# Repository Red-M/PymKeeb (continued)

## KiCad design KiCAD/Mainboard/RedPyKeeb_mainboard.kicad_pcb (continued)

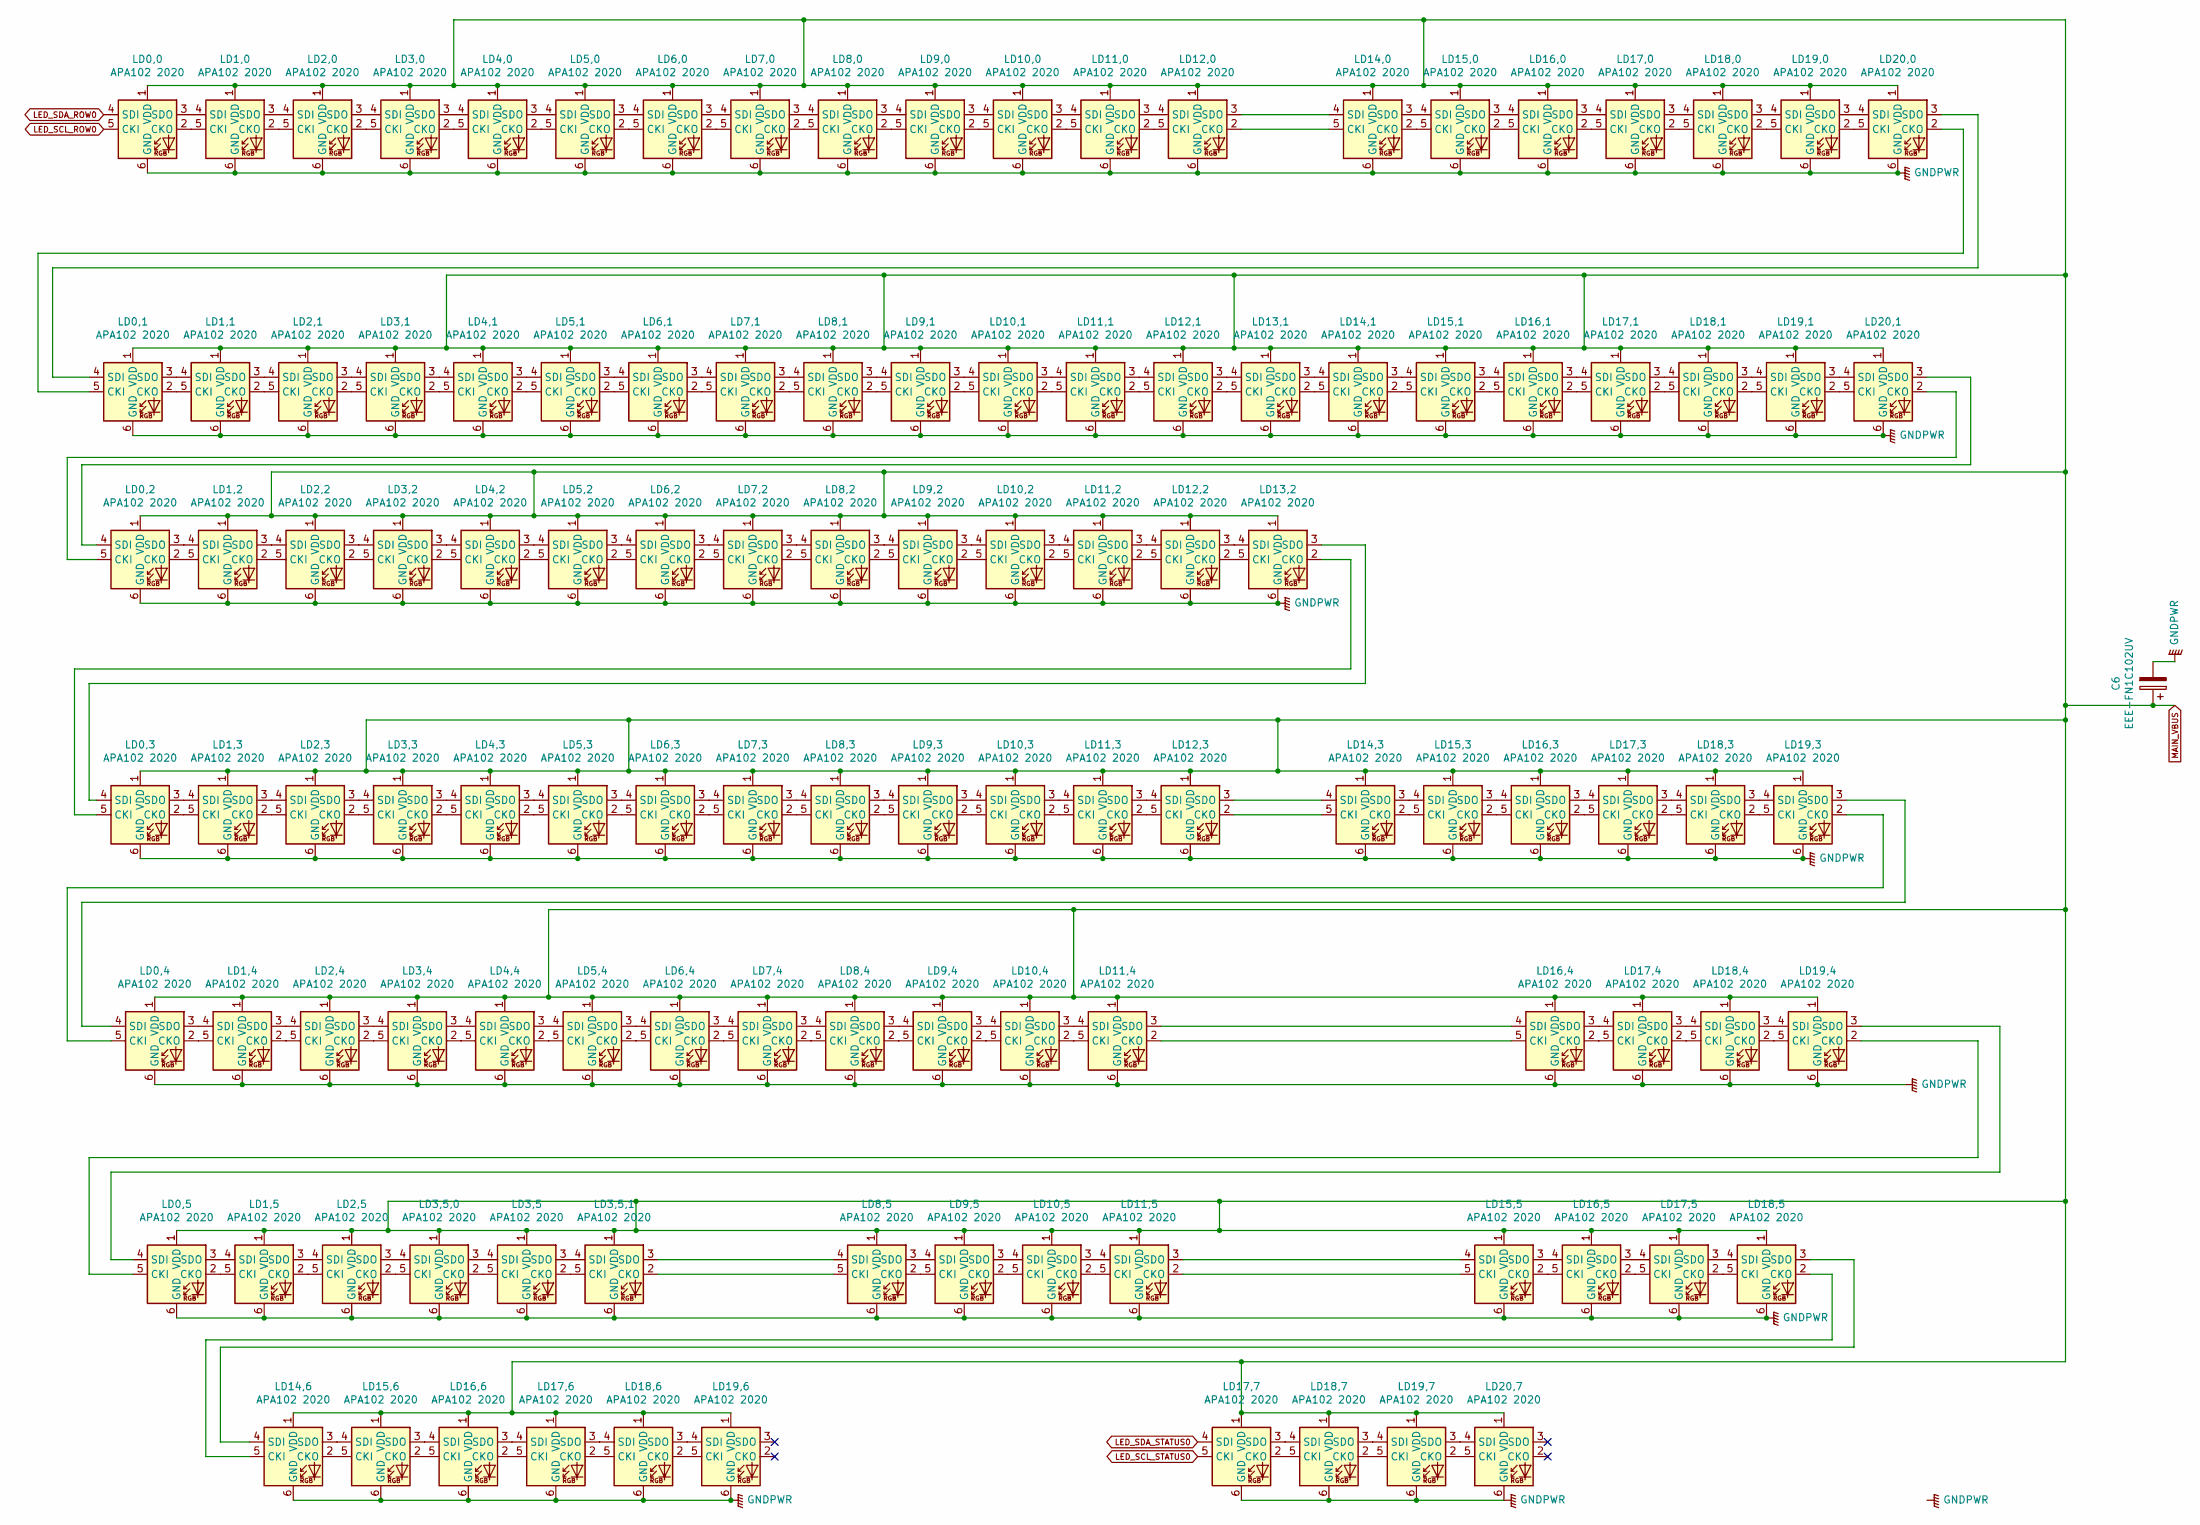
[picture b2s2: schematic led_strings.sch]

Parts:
C6: EEE-FN1C102UV; CP_Elec_10x10; Mouser No 667-EEE-FN1C102UV
LD0,0, LD0,1, LD0,2, LD0,3, LD0,4, LD0,5, LD1,0, LD1,1, LD1,2, LD1,3, LD1,4, LD1,5, LD2,0, LD2,1, LD2,2, LD2,3, LD2,4, LD2,5, LD3,0, LD3,1, LD3,2, LD3,3, LD3,4, LD3,5, LD3,5,0, LD3,5,1, LD4,0, LD4,1, LD4,2, LD4,3, LD4,4, LD5,0, LD5,1, LD5,2, LD5,3, LD5,4, LD6,0, LD6,1, LD6,2, LD6,3, LD6,4, LD7,0, LD7,1, LD7,2, LD7,3, LD7,4, LD8,0, LD8,1, LD8,2, LD8,3, LD8,4, LD8,5, LD9,0, LD9,1, LD9,2, LD9,3, LD9,4, LD9,5, LD10,0, LD10,1, LD10,2, LD10,3, LD10,4, LD10,5, LD11,0, LD11,1, LD11,2, LD11,3, LD11,4, LD11,5, LD12,0, LD12,1, LD12,2, LD12,3, LD13,1, LD13,2, LD14,0, LD14,1, LD14,3, LD14,6, LD15,0, LD15,1, LD15,3, LD15,5, LD15,6, LD16,0, LD16,1, LD16,3, LD16,4, LD16,5, LD16,6, LD17,0, LD17,1, LD17,3, LD17,4, LD17,5, LD17,6, LD17,7, LD18,0, LD18,1, LD18,3, LD18,4, LD18,5, LD18,6, LD18,7, LD19,0, LD19,1, LD19,3, LD19,4, LD19,6, LD19,7, LD20,0, LD20,1, LD20,7: APA102 2020; LED-APA102-2020; Mouser No 485-3587

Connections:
GNDPWR: C6.2, LD0,0.6 (GND), LD0,1.6 (GND), LD0,2.6 (GND), LD0,3.6 (GND), LD0,4.6 (GND), LD0,5.6 (GND), LD1,0.6 (GND), LD1,1.6 (GND), LD1,2.6 (GND), LD1,3.6 (GND), LD1,4.6 (GND), LD1,5.6 (GND), LD2,0.6 (GND), LD2,1.6 (GND), LD2,2.6 (GND), LD2,3.6 (GND), LD2,4.6 (GND), LD2,5.6 (GND), LD3,0.6 (GND), LD3,1.6 (GND), LD3,2.6 (GND), LD3,3.6 (GND), LD3,4.6 (GND), LD3,5.6 (GND), LD3,5,0.6 (GND), LD3,5,1.6 (GND), LD4,0.6 (GND), LD4,1.6 (GND), LD4,2.6 (GND), LD4,3.6 (GND), LD4,4.6 (GND), LD5,0.6 (GND), LD5,1.6 (GND), LD5,2.6 (GND), LD5,3.6 (GND), LD5,4.6 (GND), LD6,0.6 (GND), LD6,1.6 (GND), LD6,2.6 (GND), LD6,3.6 (GND), LD6,4.6 (GND), LD7,0.6 (GND), LD7,1.6 (GND), LD7,2.6 (GND), LD7,3.6 (GND), LD7,4.6 (GND), LD8,0.6 (GND), LD8,1.6 (GND), LD8,2.6 (GND), LD8,3.6 (GND), LD8,4.6 (GND), LD8,5.6 (GND), LD9,0.6 (GND), LD9,1.6 (GND), LD9,2.6 (GND), LD9,3.6 (GND), LD9,4.6 (GND), LD9,5.6 (GND), LD10,0.6 (GND), LD10,1.6 (GND), LD10,2.6 (GND), LD10,3.6 (GND), LD10,4.6 (GND), LD10,5.6 (GND), LD11,0.6 (GND), LD11,1.6 (GND), LD11,2.6 (GND), LD11,3.6 (GND), LD11,4.6 (GND), LD11,5.6 (GND), LD12,0.6 (GND), LD12,1.6 (GND), LD12,2.6 (GND), LD12,3.6 (GND), LD13,1.6 (GND), LD13,2.6 (GND), LD14,0.6 (GND), LD14,1.6 (GND), LD14,3.6 (GND), LD14,6.6 (GND), LD15,0.6 (GND), LD15,1.6 (GND), LD15,3.6 (GND), LD15,5.6 (GND), LD15,6.6 (GND), LD16,0.6 (GND), LD16,1.6 (GND), LD16,3.6 (GND), LD16,4.6 (GND), LD16,5.6 (GND), LD16,6.6 (GND), LD17,0.6 (GND), LD17,1.6 (GND), LD17,3.6 (GND), LD17,4.6 (GND), LD17,5.6 (GND), LD17,6.6 (GND), LD17,7.6 (GND), LD18,0.6 (GND), LD18,1.6 (GND), LD18,3.6 (GND), LD18,4.6 (GND), LD18,5.6 (GND), LD18,6.6 (GND), LD18,7.6 (GND), LD19,0.6 (GND), LD19,1.6 (GND), LD19,3.6 (GND), LD19,4.6 (GND), LD19,6.6 (GND), LD19,7.6 (GND), LD20,0.6 (GND), LD20,1.6 (GND), LD20,7.6 (GND); also elsewhere on the board
LED_SCL_ROW0: LD0,0.5 (CKI); also elsewhere on the board
LED_SCL_STATUS0: LD17,7.5 (CKI); also elsewhere on the board
LED_SDA_ROW0: LD0,0.4 (SDI); also elsewhere on the board
LED_SDA_STATUS0: LD17,7.4 (SDI); also elsewhere on the board
MAIN_VBUS: C6.1, LD0,0.1 (VDD), LD0,1.1 (VDD), LD0,2.1 (VDD), LD0,3.1 (VDD), LD0,4.1 (VDD), LD0,5.1 (VDD), LD1,0.1 (VDD), LD1,1.1 (VDD), LD1,2.1 (VDD), LD1,3.1 (VDD), LD1,4.1 (VDD), LD1,5.1 (VDD), LD2,0.1 (VDD), LD2,1.1 (VDD), LD2,2.1 (VDD), LD2,3.1 (VDD), LD2,4.1 (VDD), LD2,5.1 (VDD), LD3,0.1 (VDD), LD3,1.1 (VDD), LD3,2.1 (VDD), LD3,3.1 (VDD), LD3,4.1 (VDD), LD3,5.1 (VDD), LD3,5,0.1 (VDD), LD3,5,1.1 (VDD), LD4,0.1 (VDD), LD4,1.1 (VDD), LD4,2.1 (VDD), LD4,3.1 (VDD), LD4,4.1 (VDD), LD5,0.1 (VDD), LD5,1.1 (VDD), LD5,2.1 (VDD), LD5,3.1 (VDD), LD5,4.1 (VDD), LD6,0.1 (VDD), LD6,1.1 (VDD), LD6,2.1 (VDD), LD6,3.1 (VDD), LD6,4.1 (VDD), LD7,0.1 (VDD), LD7,1.1 (VDD), LD7,2.1 (VDD), LD7,3.1 (VDD), LD7,4.1 (VDD), LD8,0.1 (VDD), LD8,1.1 (VDD), LD8,2.1 (VDD), LD8,3.1 (VDD), LD8,4.1 (VDD), LD8,5.1 (VDD), LD9,0.1 (VDD), LD9,1.1 (VDD), LD9,2.1 (VDD), LD9,3.1 (VDD), LD9,4.1 (VDD), LD9,5.1 (VDD), LD10,0.1 (VDD), LD10,1.1 (VDD), LD10,2.1 (VDD), LD10,3.1 (VDD), LD10,4.1 (VDD), LD10,5.1 (VDD), LD11,0.1 (VDD), LD11,1.1 (VDD), LD11,2.1 (VDD), LD11,3.1 (VDD), LD11,4.1 (VDD), LD11,5.1 (VDD), LD12,0.1 (VDD), LD12,1.1 (VDD), LD12,2.1 (VDD), LD12,3.1 (VDD), LD13,1.1 (VDD), LD13,2.1 (VDD), LD14,0.1 (VDD), LD14,1.1 (VDD), LD14,3.1 (VDD), LD14,6.1 (VDD), LD15,0.1 (VDD), LD15,1.1 (VDD), LD15,3.1 (VDD), LD15,5.1 (VDD), LD15,6.1 (VDD), LD16,0.1 (VDD), LD16,1.1 (VDD), LD16,3.1 (VDD), LD16,4.1 (VDD), LD16,5.1 (VDD), LD16,6.1 (VDD), LD17,0.1 (VDD), LD17,1.1 (VDD), LD17,3.1 (VDD), LD17,4.1 (VDD), LD17,5.1 (VDD), LD17,6.1 (VDD), LD17,7.1 (VDD), LD18,0.1 (VDD), LD18,1.1 (VDD), LD18,3.1 (VDD), LD18,4.1 (VDD), LD18,5.1 (VDD), LD18,6.1 (VDD), LD18,7.1 (VDD), LD19,0.1 (VDD), LD19,1.1 (VDD), LD19,3.1 (VDD), LD19,4.1 (VDD), LD19,6.1 (VDD), LD19,7.1 (VDD), LD20,0.1 (VDD), LD20,1.1 (VDD), LD20,7.1 (VDD); also elsewhere on the board
unnamed: LD0,0.2 (CKO), LD1,0.5 (CKI)
unnamed: LD0,0.3 (SDO), LD1,0.4 (SDI)
unnamed: LD0,1.2 (CKO), LD1,1.5 (CKI)
unnamed: LD0,1.3 (SDO), LD1,1.4 (SDI)
unnamed: LD0,1.4 (SDI), LD20,0.3 (SDO)
unnamed: LD0,1.5 (CKI), LD20,0.2 (CKO)
unnamed: LD0,2.2 (CKO), LD1,2.5 (CKI)
unnamed: LD0,2.3 (SDO), LD1,2.4 (SDI)
unnamed: LD0,2.4 (SDI), LD20,1.3 (SDO)
unnamed: LD0,2.5 (CKI), LD20,1.2 (CKO)
unnamed: LD0,3.2 (CKO), LD1,3.5 (CKI)
unnamed: LD0,3.3 (SDO), LD1,3.4 (SDI)
unnamed: LD0,3.4 (SDI), LD13,2.3 (SDO)
unnamed: LD0,3.5 (CKI), LD13,2.2 (CKO)
unnamed: LD0,4.2 (CKO), LD1,4.5 (CKI)
unnamed: LD0,4.3 (SDO), LD1,4.4 (SDI)
unnamed: LD0,4.4 (SDI), LD19,3.3 (SDO)
unnamed: LD0,4.5 (CKI), LD19,3.2 (CKO)
unnamed: LD0,5.2 (CKO), LD1,5.5 (CKI)
unnamed: LD0,5.3 (SDO), LD1,5.4 (SDI)
unnamed: LD0,5.4 (SDI), LD19,4.3 (SDO)
unnamed: LD0,5.5 (CKI), LD19,4.2 (CKO)
unnamed: LD1,0.2 (CKO), LD2,0.5 (CKI)
unnamed: LD1,0.3 (SDO), LD2,0.4 (SDI)
unnamed: LD1,1.2 (CKO), LD2,1.5 (CKI)
unnamed: LD1,1.3 (SDO), LD2,1.4 (SDI)
unnamed: LD1,2.2 (CKO), LD2,2.5 (CKI)
unnamed: LD1,2.3 (SDO), LD2,2.4 (SDI)
unnamed: LD1,3.2 (CKO), LD2,3.5 (CKI)
unnamed: LD1,3.3 (SDO), LD2,3.4 (SDI)
unnamed: LD1,4.2 (CKO), LD2,4.5 (CKI)
unnamed: LD1,4.3 (SDO), LD2,4.4 (SDI)
unnamed: LD1,5.2 (CKO), LD2,5.5 (CKI)
unnamed: LD1,5.3 (SDO), LD2,5.4 (SDI)
unnamed: LD2,0.2 (CKO), LD3,0.5 (CKI)
unnamed: LD2,0.3 (SDO), LD3,0.4 (SDI)
unnamed: LD2,1.2 (CKO), LD3,1.5 (CKI)
unnamed: LD2,1.3 (SDO), LD3,1.4 (SDI)
unnamed: LD2,2.2 (CKO), LD3,2.5 (CKI)
unnamed: LD2,2.3 (SDO), LD3,2.4 (SDI)
unnamed: LD2,3.2 (CKO), LD3,3.5 (CKI)
unnamed: LD2,3.3 (SDO), LD3,3.4 (SDI)
unnamed: LD2,4.2 (CKO), LD3,4.5 (CKI)
unnamed: LD2,4.3 (SDO), LD3,4.4 (SDI)
unnamed: LD2,5.2 (CKO), LD3,5,0.5 (CKI)
unnamed: LD2,5.3 (SDO), LD3,5,0.4 (SDI)
unnamed: LD3,0.2 (CKO), LD4,0.5 (CKI)
unnamed: LD3,0.3 (SDO), LD4,0.4 (SDI)
unnamed: LD3,1.2 (CKO), LD4,1.5 (CKI)
unnamed: LD3,1.3 (SDO), LD4,1.4 (SDI)
unnamed: LD3,2.2 (CKO), LD4,2.5 (CKI)
unnamed: LD3,2.3 (SDO), LD4,2.4 (SDI)
unnamed: LD3,3.2 (CKO), LD4,3.5 (CKI)
unnamed: LD3,3.3 (SDO), LD4,3.4 (SDI)
unnamed: LD3,4.2 (CKO), LD4,4.5 (CKI)
unnamed: LD3,4.3 (SDO), LD4,4.4 (SDI)
unnamed: LD3,5.5 (CKI), LD3,5,0.2 (CKO)
unnamed: LD3,5.4 (SDI), LD3,5,0.3 (SDO)
unnamed: LD3,5,1.2 (CKO), LD8,5.5 (CKI)
unnamed: LD3,5,1.3 (SDO), LD8,5.4 (SDI)
unnamed: LD3,5.3 (SDO), LD3,5,1.4 (SDI)
unnamed: LD3,5.2 (CKO), LD3,5,1.5 (CKI)
unnamed: LD4,0.2 (CKO), LD5,0.5 (CKI)
unnamed: LD4,0.3 (SDO), LD5,0.4 (SDI)
unnamed: LD4,1.2 (CKO), LD5,1.5 (CKI)
unnamed: LD4,1.3 (SDO), LD5,1.4 (SDI)
unnamed: LD4,2.2 (CKO), LD5,2.5 (CKI)
unnamed: LD4,2.3 (SDO), LD5,2.4 (SDI)
unnamed: LD4,3.2 (CKO), LD5,3.5 (CKI)
unnamed: LD4,3.3 (SDO), LD5,3.4 (SDI)
unnamed: LD4,4.2 (CKO), LD5,4.5 (CKI)
unnamed: LD4,4.3 (SDO), LD5,4.4 (SDI)
unnamed: LD5,0.2 (CKO), LD6,0.5 (CKI)
unnamed: LD5,0.3 (SDO), LD6,0.4 (SDI)
unnamed: LD5,1.2 (CKO), LD6,1.5 (CKI)
unnamed: LD5,1.3 (SDO), LD6,1.4 (SDI)
unnamed: LD5,2.2 (CKO), LD6,2.5 (CKI)
unnamed: LD5,2.3 (SDO), LD6,2.4 (SDI)
unnamed: LD5,3.2 (CKO), LD6,3.5 (CKI)
unnamed: LD5,3.3 (SDO), LD6,3.4 (SDI)
unnamed: LD5,4.2 (CKO), LD6,4.5 (CKI)
unnamed: LD5,4.3 (SDO), LD6,4.4 (SDI)
unnamed: LD6,0.2 (CKO), LD7,0.5 (CKI)
unnamed: LD6,0.3 (SDO), LD7,0.4 (SDI)
unnamed: LD6,1.2 (CKO), LD7,1.5 (CKI)
unnamed: LD6,1.3 (SDO), LD7,1.4 (SDI)
unnamed: LD6,2.2 (CKO), LD7,2.5 (CKI)
unnamed: LD6,2.3 (SDO), LD7,2.4 (SDI)
unnamed: LD6,3.2 (CKO), LD7,3.5 (CKI)
unnamed: LD6,3.3 (SDO), LD7,3.4 (SDI)
unnamed: LD6,4.2 (CKO), LD7,4.5 (CKI)
unnamed: LD6,4.3 (SDO), LD7,4.4 (SDI)
unnamed: LD7,0.2 (CKO), LD8,0.5 (CKI)
unnamed: LD7,0.3 (SDO), LD8,0.4 (SDI)
unnamed: LD7,1.2 (CKO), LD8,1.5 (CKI)
unnamed: LD7,1.3 (SDO), LD8,1.4 (SDI)
unnamed: LD7,2.2 (CKO), LD8,2.5 (CKI)
unnamed: LD7,2.3 (SDO), LD8,2.4 (SDI)
unnamed: LD7,3.2 (CKO), LD8,3.5 (CKI)
unnamed: LD7,3.3 (SDO), LD8,3.4 (SDI)
unnamed: LD7,4.2 (CKO), LD8,4.5 (CKI)
unnamed: LD7,4.3 (SDO), LD8,4.4 (SDI)
unnamed: LD8,0.2 (CKO), LD9,0.5 (CKI)
unnamed: LD8,0.3 (SDO), LD9,0.4 (SDI)
unnamed: LD8,1.2 (CKO), LD9,1.5 (CKI)
unnamed: LD8,1.3 (SDO), LD9,1.4 (SDI)
unnamed: LD8,2.2 (CKO), LD9,2.5 (CKI)
unnamed: LD8,2.3 (SDO), LD9,2.4 (SDI)
unnamed: LD8,3.2 (CKO), LD9,3.5 (CKI)
unnamed: LD8,3.3 (SDO), LD9,3.4 (SDI)
unnamed: LD8,4.2 (CKO), LD9,4.5 (CKI)
unnamed: LD8,4.3 (SDO), LD9,4.4 (SDI)
unnamed: LD8,5.2 (CKO), LD9,5.5 (CKI)
unnamed: LD8,5.3 (SDO), LD9,5.4 (SDI)
unnamed: LD10,0.2 (CKO), LD11,0.5 (CKI)
unnamed: LD10,0.3 (SDO), LD11,0.4 (SDI)
unnamed: LD9,0.3 (SDO), LD10,0.4 (SDI)
unnamed: LD9,0.2 (CKO), LD10,0.5 (CKI)
unnamed: LD10,1.2 (CKO), LD11,1.5 (CKI)
unnamed: LD10,1.3 (SDO), LD11,1.4 (SDI)
unnamed: LD9,1.3 (SDO), LD10,1.4 (SDI)
unnamed: LD9,1.2 (CKO), LD10,1.5 (CKI)
unnamed: LD10,2.2 (CKO), LD11,2.5 (CKI)
unnamed: LD10,2.3 (SDO), LD11,2.4 (SDI)
unnamed: LD9,2.3 (SDO), LD10,2.4 (SDI)
unnamed: LD9,2.2 (CKO), LD10,2.5 (CKI)
unnamed: LD10,3.2 (CKO), LD11,3.5 (CKI)
unnamed: LD10,3.3 (SDO), LD11,3.4 (SDI)
unnamed: LD9,3.3 (SDO), LD10,3.4 (SDI)
unnamed: LD9,3.2 (CKO), LD10,3.5 (CKI)
unnamed: LD10,4.2 (CKO), LD11,4.5 (CKI)
unnamed: LD10,4.3 (SDO), LD11,4.4 (SDI)
unnamed: LD9,4.3 (SDO), LD10,4.4 (SDI)
unnamed: LD9,4.2 (CKO), LD10,4.5 (CKI)
unnamed: LD10,5.2 (CKO), LD11,5.5 (CKI)
unnamed: LD10,5.3 (SDO), LD11,5.4 (SDI)
unnamed: LD9,5.3 (SDO), LD10,5.4 (SDI)
unnamed: LD9,5.2 (CKO), LD10,5.5 (CKI)
unnamed: LD11,0.2 (CKO), LD12,0.5 (CKI)
unnamed: LD11,0.3 (SDO), LD12,0.4 (SDI)
unnamed: LD11,1.2 (CKO), LD12,1.5 (CKI)
unnamed: LD11,1.3 (SDO), LD12,1.4 (SDI)
unnamed: LD11,2.2 (CKO), LD12,2.5 (CKI)
unnamed: LD11,2.3 (SDO), LD12,2.4 (SDI)
unnamed: LD11,3.2 (CKO), LD12,3.5 (CKI)
unnamed: LD11,3.3 (SDO), LD12,3.4 (SDI)
unnamed: LD11,4.2 (CKO), LD16,4.5 (CKI)
unnamed: LD11,4.3 (SDO), LD16,4.4 (SDI)
unnamed: LD11,5.2 (CKO), LD15,5.5 (CKI)
unnamed: LD11,5.3 (SDO), LD15,5.4 (SDI)
unnamed: LD12,0.2 (CKO), LD14,0.5 (CKI)
unnamed: LD12,0.3 (SDO), LD14,0.4 (SDI)
unnamed: LD12,1.2 (CKO), LD13,1.5 (CKI)
unnamed: LD12,1.3 (SDO), LD13,1.4 (SDI)
unnamed: LD12,2.2 (CKO), LD13,2.5 (CKI)
unnamed: LD12,2.3 (SDO), LD13,2.4 (SDI)
unnamed: LD12,3.2 (CKO), LD14,3.5 (CKI)
unnamed: LD12,3.3 (SDO), LD14,3.4 (SDI)
unnamed: LD13,1.2 (CKO), LD14,1.5 (CKI)
unnamed: LD13,1.3 (SDO), LD14,1.4 (SDI)
unnamed: LD14,0.2 (CKO), LD15,0.5 (CKI)
unnamed: LD14,0.3 (SDO), LD15,0.4 (SDI)
unnamed: LD14,1.2 (CKO), LD15,1.5 (CKI)
unnamed: LD14,1.3 (SDO), LD15,1.4 (SDI)
unnamed: LD14,3.2 (CKO), LD15,3.5 (CKI)
unnamed: LD14,3.3 (SDO), LD15,3.4 (SDI)
unnamed: LD14,6.2 (CKO), LD15,6.5 (CKI)
unnamed: LD14,6.3 (SDO), LD15,6.4 (SDI)
unnamed: LD14,6.4 (SDI), LD18,5.3 (SDO)
unnamed: LD14,6.5 (CKI), LD18,5.2 (CKO)
unnamed: LD15,0.2 (CKO), LD16,0.5 (CKI)
unnamed: LD15,0.3 (SDO), LD16,0.4 (SDI)
unnamed: LD15,1.2 (CKO), LD16,1.5 (CKI)
unnamed: LD15,1.3 (SDO), LD16,1.4 (SDI)
unnamed: LD15,3.2 (CKO), LD16,3.5 (CKI)
unnamed: LD15,3.3 (SDO), LD16,3.4 (SDI)
unnamed: LD15,5.2 (CKO), LD16,5.5 (CKI)
unnamed: LD15,5.3 (SDO), LD16,5.4 (SDI)
unnamed: LD15,6.2 (CKO), LD16,6.5 (CKI)
unnamed: LD15,6.3 (SDO), LD16,6.4 (SDI)
unnamed: LD16,0.2 (CKO), LD17,0.5 (CKI)
unnamed: LD16,0.3 (SDO), LD17,0.4 (SDI)
unnamed: LD16,1.2 (CKO), LD17,1.5 (CKI)
unnamed: LD16,1.3 (SDO), LD17,1.4 (SDI)
unnamed: LD16,3.2 (CKO), LD17,3.5 (CKI)
unnamed: LD16,3.3 (SDO), LD17,3.4 (SDI)
unnamed: LD16,4.2 (CKO), LD17,4.5 (CKI)
unnamed: LD16,4.3 (SDO), LD17,4.4 (SDI)
unnamed: LD16,5.2 (CKO), LD17,5.5 (CKI)
unnamed: LD16,5.3 (SDO), LD17,5.4 (SDI)
unnamed: LD16,6.2 (CKO), LD17,6.5 (CKI)
unnamed: LD16,6.3 (SDO), LD17,6.4 (SDI)
unnamed: LD17,0.2 (CKO), LD18,0.5 (CKI)
unnamed: LD17,0.3 (SDO), LD18,0.4 (SDI)
unnamed: LD17,1.2 (CKO), LD18,1.5 (CKI)
unnamed: LD17,1.3 (SDO), LD18,1.4 (SDI)
unnamed: LD17,3.2 (CKO), LD18,3.5 (CKI)
unnamed: LD17,3.3 (SDO), LD18,3.4 (SDI)
unnamed: LD17,4.2 (CKO), LD18,4.5 (CKI)
unnamed: LD17,4.3 (SDO), LD18,4.4 (SDI)
unnamed: LD17,5.2 (CKO), LD18,5.5 (CKI)
unnamed: LD17,5.3 (SDO), LD18,5.4 (SDI)
unnamed: LD17,6.2 (CKO), LD18,6.5 (CKI)
unnamed: LD17,6.3 (SDO), LD18,6.4 (SDI)
unnamed: LD17,7.2 (CKO), LD18,7.5 (CKI)
unnamed: LD17,7.3 (SDO), LD18,7.4 (SDI)
unnamed: LD18,0.2 (CKO), LD19,0.5 (CKI)
unnamed: LD18,0.3 (SDO), LD19,0.4 (SDI)
unnamed: LD18,1.2 (CKO), LD19,1.5 (CKI)
unnamed: LD18,1.3 (SDO), LD19,1.4 (SDI)
unnamed: LD18,3.2 (CKO), LD19,3.5 (CKI)
unnamed: LD18,3.3 (SDO), LD19,3.4 (SDI)
unnamed: LD18,4.2 (CKO), LD19,4.5 (CKI)
unnamed: LD18,4.3 (SDO), LD19,4.4 (SDI)
unnamed: LD18,6.2 (CKO), LD19,6.5 (CKI)
unnamed: LD18,6.3 (SDO), LD19,6.4 (SDI)
unnamed: LD18,7.2 (CKO), LD19,7.5 (CKI)
unnamed: LD18,7.3 (SDO), LD19,7.4 (SDI)
unnamed: LD19,0.2 (CKO), LD20,0.5 (CKI)
unnamed: LD19,0.3 (SDO), LD20,0.4 (SDI)
unnamed: LD19,1.2 (CKO), LD20,1.5 (CKI)
unnamed: LD19,1.3 (SDO), LD20,1.4 (SDI)
unnamed: LD19,7.2 (CKO), LD20,7.5 (CKI)
unnamed: LD19,7.3 (SDO), LD20,7.4 (SDI)

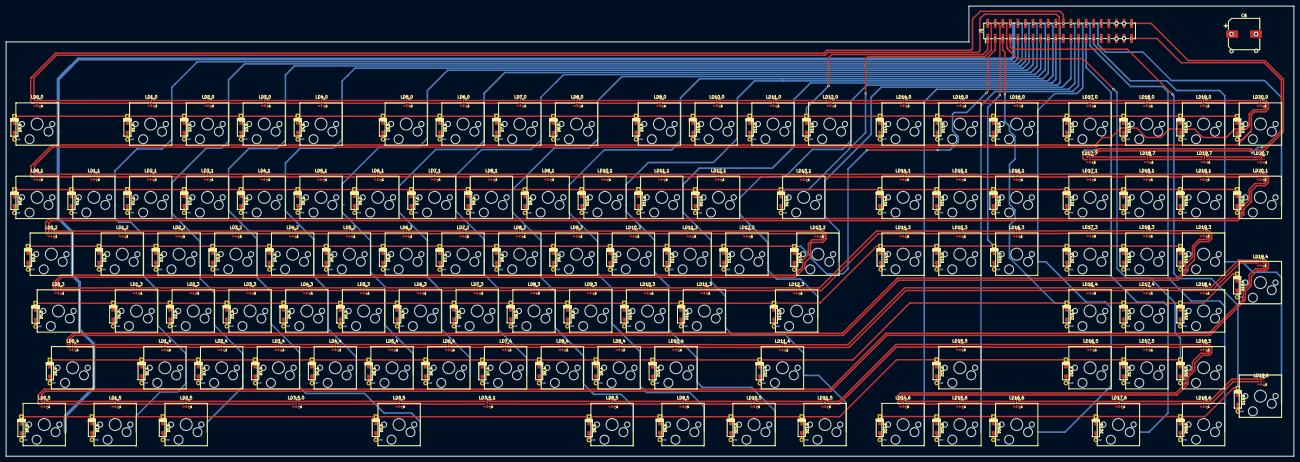
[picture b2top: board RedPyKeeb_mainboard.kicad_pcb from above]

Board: 4 copper layers, 432.0 x 151.0 mm, 333 parts (1 on the bottom side), 366 nets.

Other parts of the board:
C6#2: EEE-FN1C102UV; CP_Elec_10x10

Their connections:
GNDPWR: C6#2.2; also elsewhere on the board
MAIN_VBUS: C6#2.1; also elsewhere on the board

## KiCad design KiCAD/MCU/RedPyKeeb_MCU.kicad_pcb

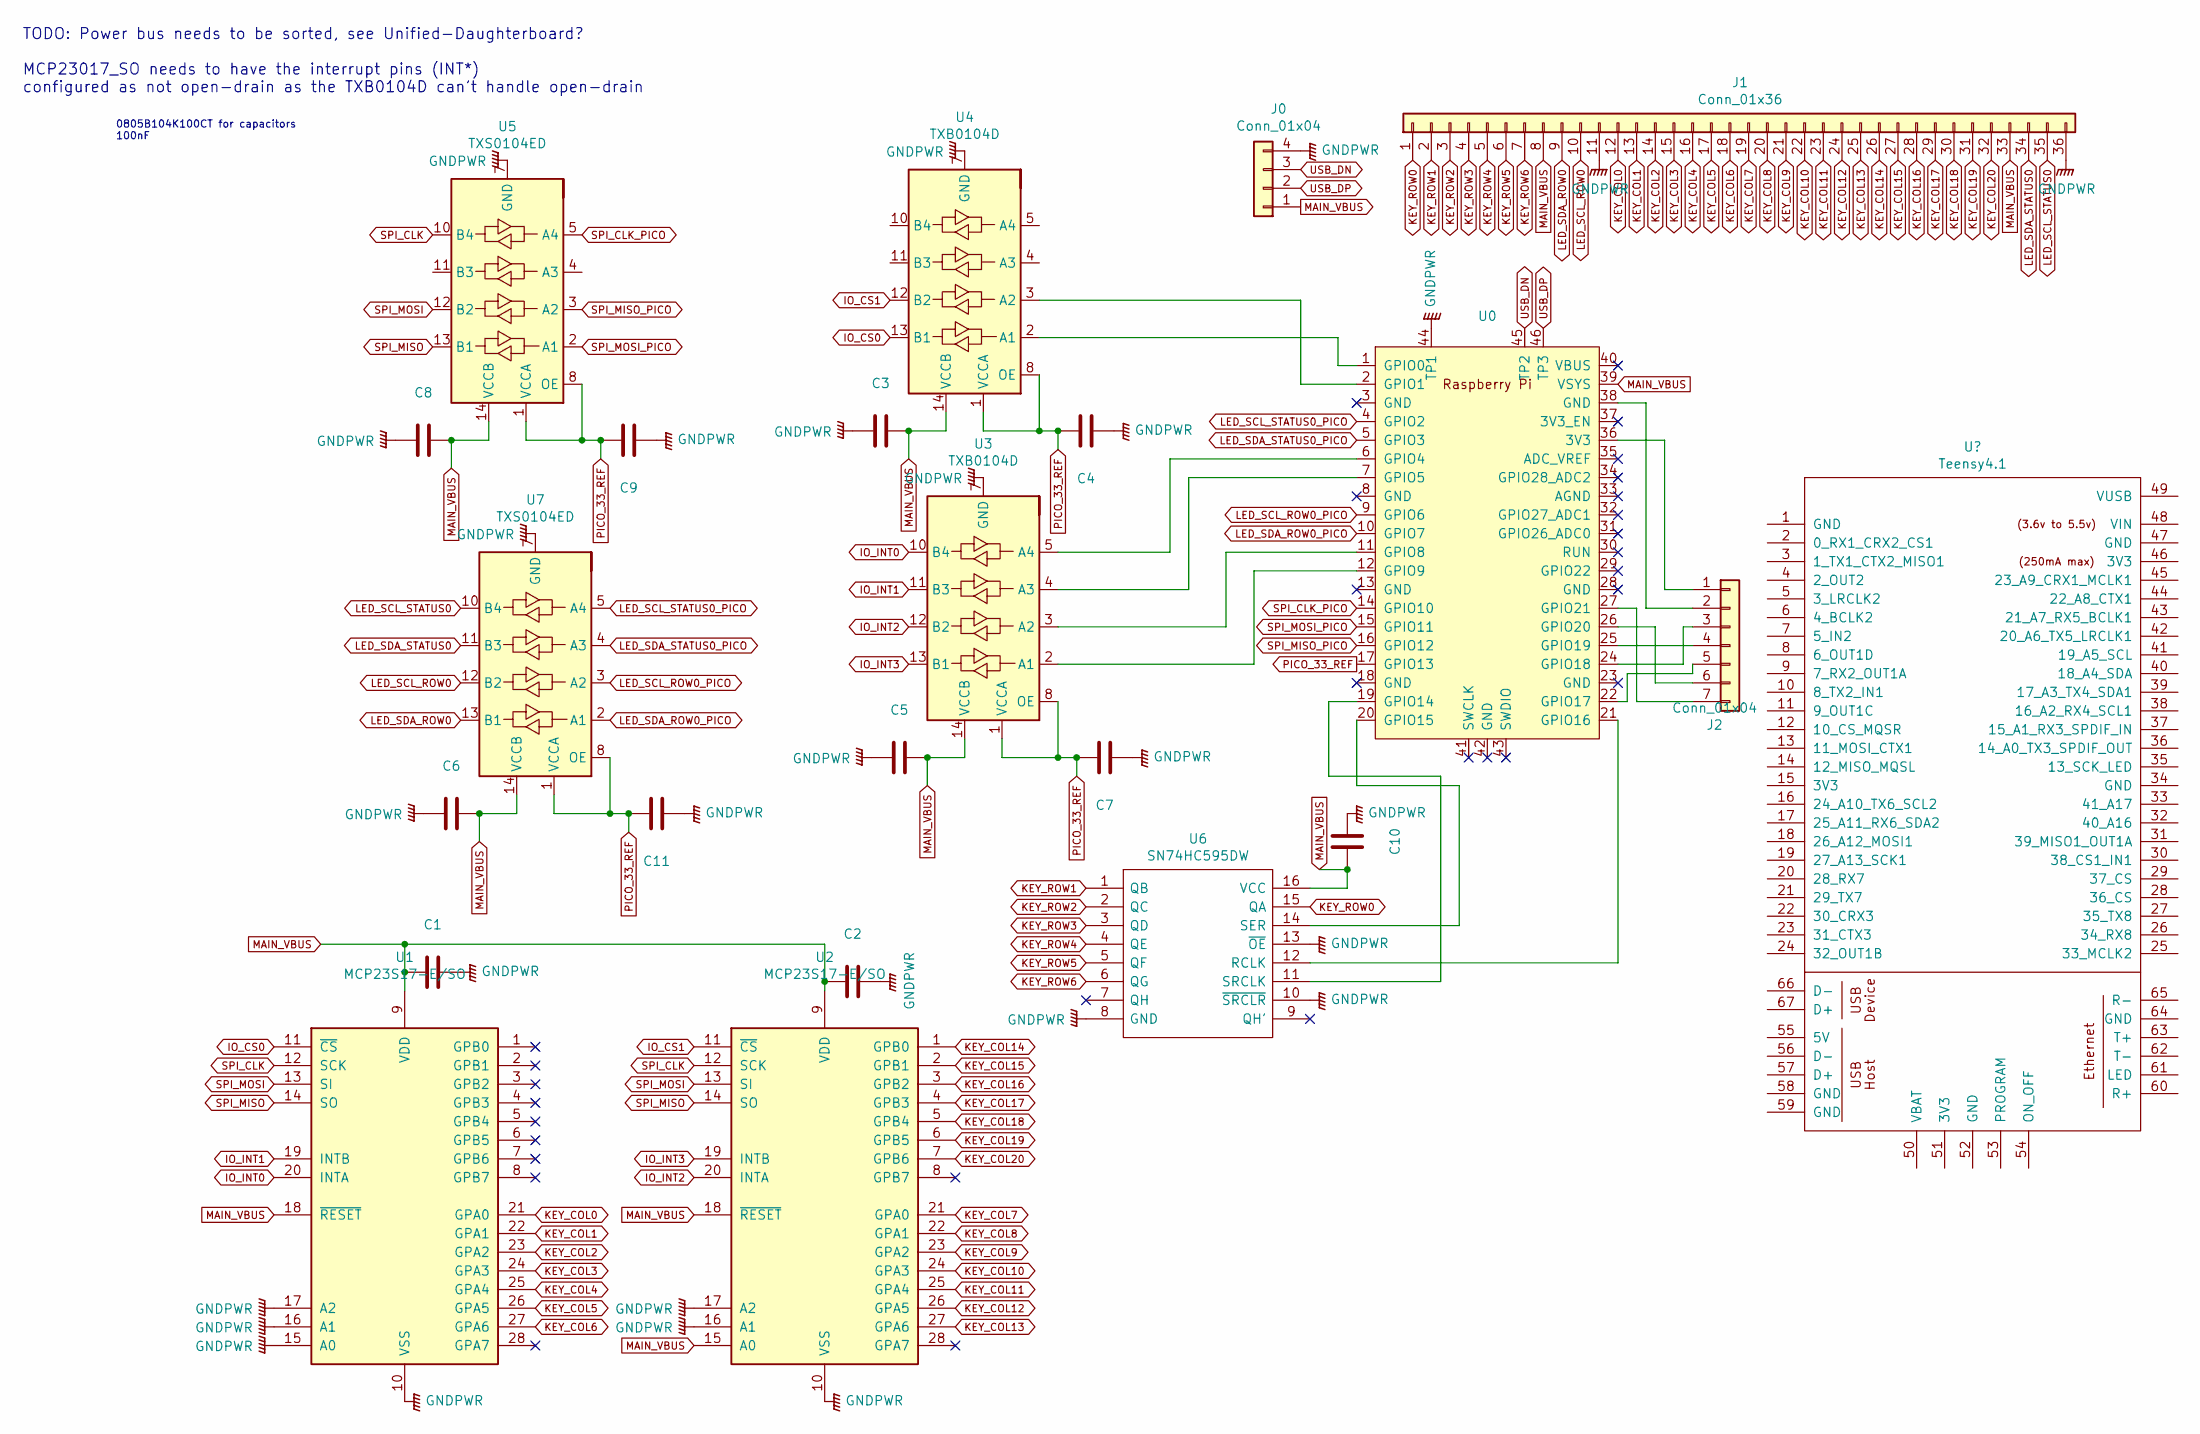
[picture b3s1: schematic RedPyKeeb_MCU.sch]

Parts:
C1, C2: 0805B104K100CT; C_0805_HandSoldering; Mouser No 791-0805B104K100CT
C3, C4, C5, C6, C7, C8, C9, C10, C11: 0805B101K100CT; C_0805_2012Metric_Pad1.18x1.45mm_HandSolder; Mouser No 791-0805B101K100CT
J0: Conn_01x04; JST_EH_S4B-EH_1x04_P2.50mm_Horizontal; Mouser No 485-3955
J1: Conn_01x36; PinHeader_1x36_P2.00mm_Horizontal
J2: Conn_01x04; JST_EH_S7B-EH_1x07_P2.50mm_Horizontal; Mouser No 485-3955
U0: RPi_Pico_SMD_TH
U1, U2: MCP23S17-E/SO; SOIC-28W_7.5x17.9mm_P1.27mm; Mouser No 579-MCP23S17-E/SO
U3, U4: TXB0104D; SOIC-14_3.9x8.7mm_P1.27mm; Mouser No 595-TXB0104D
U5, U7: TXS0104ED; SOIC-14_3.9x8.7mm_P1.27mm; Mouser No 595-TXS0104ED
U6: SN74HC595DW; SOIC-16W_7.5x10.3mm_P1.27mm; Mouser Part Number 595-SN74HC595DW

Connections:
GNDPWR: C1.2, C2.2, C3.1, C4.1, C5.1, C6.1, C7.1, C8.1, C9.1, C10.1, C11.1, J0.4, J1.11, J1.36, U0.44 (TP1), U1.10 (VSS), U1.15 (A0), U1.16 (A1), U1.17 (A2), U2.10 (VSS), U2.16 (A1), U2.17 (A2), U3.7 (GND), U4.7 (GND), U5.7 (GND), U6.8 (GND), U6.10 (~SRCLR), U6.13 (~OE), U7.7 (GND)
IO_CS0: U1.11 (~CS~), U4.13 (B1)
IO_CS1: U2.11 (~CS~), U4.12 (B2)
IO_INT0: U1.20 (INTA), U3.10 (B4)
IO_INT1: U1.19 (INTB), U3.11 (B3)
IO_INT2: U2.20 (INTA), U3.12 (B2)
IO_INT3: U2.19 (INTB), U3.13 (B1)
KEY_COL0: J1.12, U1.21 (GPA0)
KEY_COL1: J1.13, U1.22 (GPA1)
KEY_COL2: J1.14, U1.23 (GPA2)
KEY_COL3: J1.15, U1.24 (GPA3)
KEY_COL4: J1.16, U1.25 (GPA4)
KEY_COL5: J1.17, U1.26 (GPA5)
KEY_COL6: J1.18, U1.27 (GPA6)
KEY_COL7: J1.19, U2.21 (GPA0)
KEY_COL8: J1.20, U2.22 (GPA1)
KEY_COL9: J1.21, U2.23 (GPA2)
KEY_COL10: J1.22, U2.24 (GPA3)
KEY_COL11: J1.23, U2.25 (GPA4)
KEY_COL12: J1.24, U2.26 (GPA5)
KEY_COL13: J1.25, U2.27 (GPA6)
KEY_COL14: J1.26, U2.1 (GPB0)
KEY_COL15: J1.27, U2.2 (GPB1)
KEY_COL16: J1.28, U2.3 (GPB2)
KEY_COL17: J1.29, U2.4 (GPB3)
KEY_COL18: J1.30, U2.5 (GPB4)
KEY_COL19: J1.31, U2.6 (GPB5)
KEY_COL20: J1.32, U2.7 (GPB6)
KEY_ROW0: J1.1, U6.15 (QA)
KEY_ROW1: J1.2, U6.1 (QB)
KEY_ROW2: J1.3, U6.2 (QC)
KEY_ROW3: J1.4, U6.3 (QD)
KEY_ROW4: J1.5, U6.4 (QE)
KEY_ROW5: J1.6, U6.5 (QF)
KEY_ROW6: J1.7, U6.6 (QG)
LED_SCL_ROW0: J1.10, U7.12 (B2)
LED_SCL_ROW0_PICO: U0.9 (GPIO6), U7.3 (A2)
LED_SCL_STATUS0: J1.35, U7.10 (B4)
LED_SCL_STATUS0_PICO: U0.4 (GPIO2), U7.5 (A4)
LED_SDA_ROW0: J1.9, U7.13 (B1)
LED_SDA_ROW0_PICO: U0.10 (GPIO7), U7.2 (A1)
LED_SDA_STATUS0: J1.34, U7.11 (B3)
LED_SDA_STATUS0_PICO: U0.5 (GPIO3), U7.4 (A3)
MAIN_VBUS: C1.1, C2.1, C3.2, C5.2, C6.2, C8.2, C10.2, J0.1, J1.8, J1.33, U0.39 (VSYS), U1.9 (VDD), U1.18 (~RESET~), U2.9 (VDD), U2.15 (A0), U2.18 (~RESET~), U3.14 (VCCB), U4.14 (VCCB), U5.14 (VCCB), U6.16 (VCC), U7.14 (VCCB)
unnamed: J2.1, U0.36 (3V3)
unnamed: J2.2, U0.38 (GND)
unnamed: J2.3, U0.24 (GPIO18)
unnamed: J2.4, U0.25 (GPIO19)
unnamed: J2.5, U0.22 (GPIO17)
unnamed: J2.6, U0.26 (GPIO20)
unnamed: J2.7, U0.27 (GPIO21)
unnamed: U0.1 (GPIO0), U4.2 (A1)
unnamed: U0.2 (GPIO1), U4.3 (A2)
unnamed: U0.6 (GPIO4), U3.5 (A4)
unnamed: U0.7 (GPIO5), U3.4 (A3)
unnamed: U0.11 (GPIO8), U3.3 (A2)
unnamed: U0.12 (GPIO9), U3.2 (A1)
unnamed: U0.19 (GPIO14), U6.11 (SRCLK)
unnamed: U0.20 (GPIO15), U6.14 (SER)
unnamed: U0.21 (GPIO16), U6.12 (RCLK)
PICO_33_REF: C4.2, C7.2, C9.2, C11.2, U0.17 (GPIO13), U3.1 (VCCA), U3.8 (OE), U4.1 (VCCA), U4.8 (OE), U5.1 (VCCA), U5.8 (OE), U7.1 (VCCA), U7.8 (OE)
SPI_CLK: U1.12 (SCK), U2.12 (SCK), U5.10 (B4)
SPI_CLK_PICO: U0.14 (GPIO10), U5.5 (A4)
SPI_MISO: U1.14 (SO), U2.14 (SO), U5.13 (B1)
SPI_MISO_PICO: U0.16 (GPIO12), U5.3 (A2)
SPI_MOSI: U1.13 (SI), U2.13 (SI), U5.12 (B2)
SPI_MOSI_PICO: U0.15 (GPIO11), U5.2 (A1)
USB_DN: J0.3, U0.45 (TP2)
USB_DP: J0.2, U0.46 (TP3)

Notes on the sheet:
TODO: Power bus needs to be sorted, see Unified-Daughterboard? MCP23017_SO needs to have the interrupt pins (INT*) configured as not open-drain as the TXB0104D can't handle open-drain
0805B104K100CT for capacitors 100nF

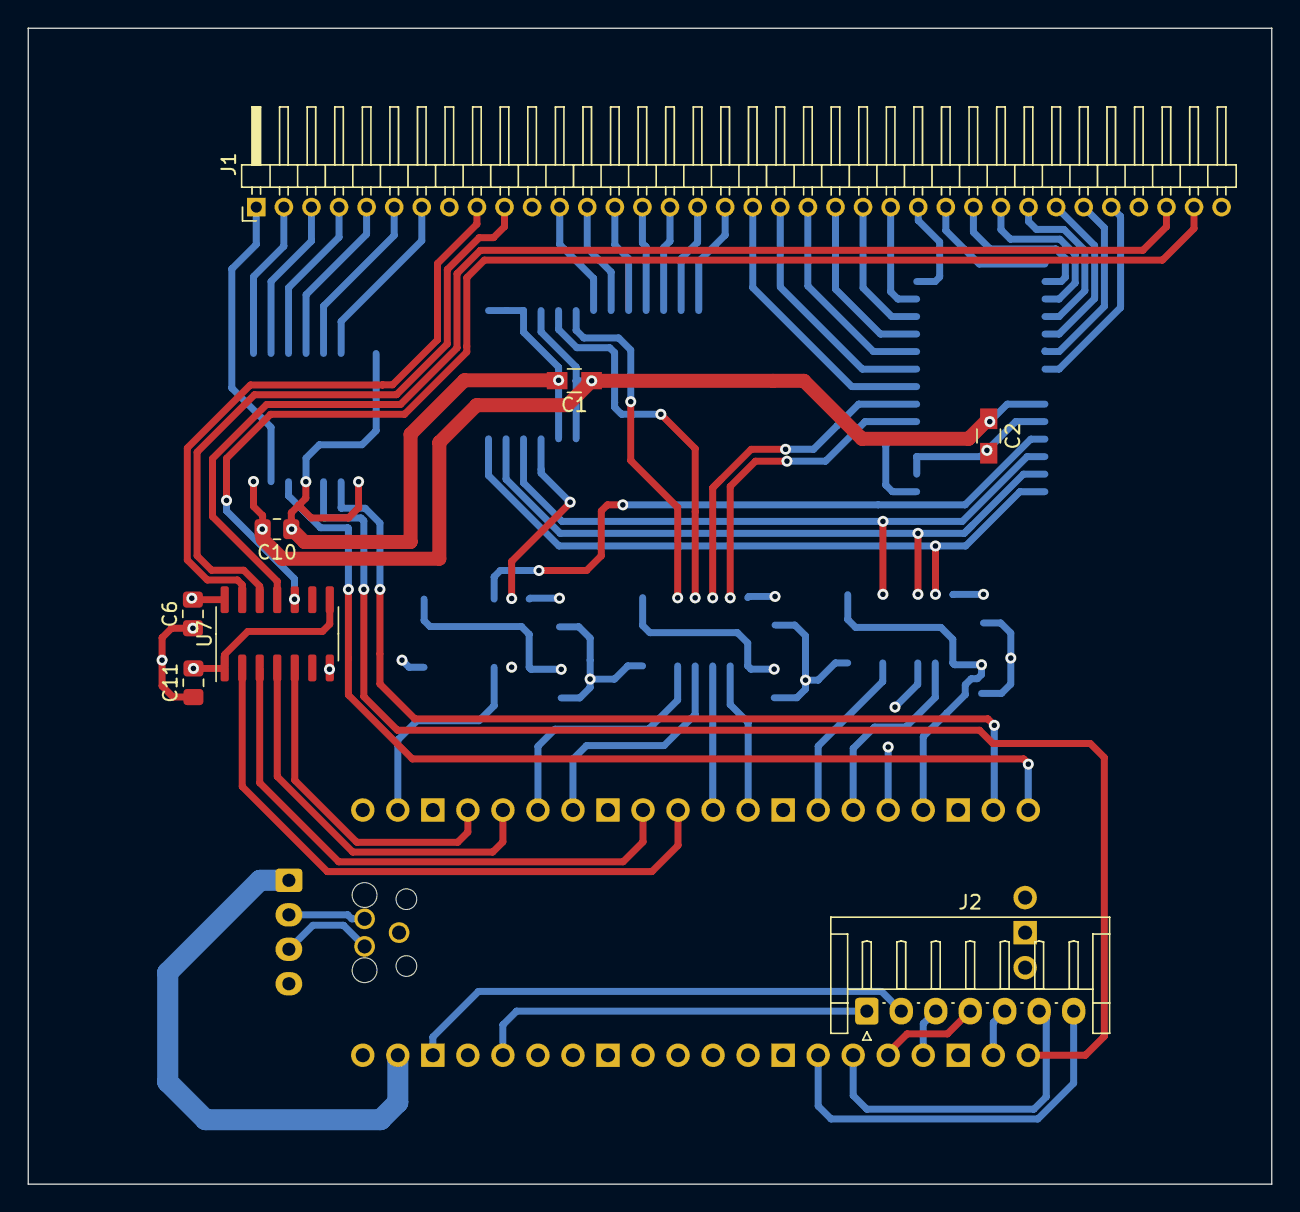
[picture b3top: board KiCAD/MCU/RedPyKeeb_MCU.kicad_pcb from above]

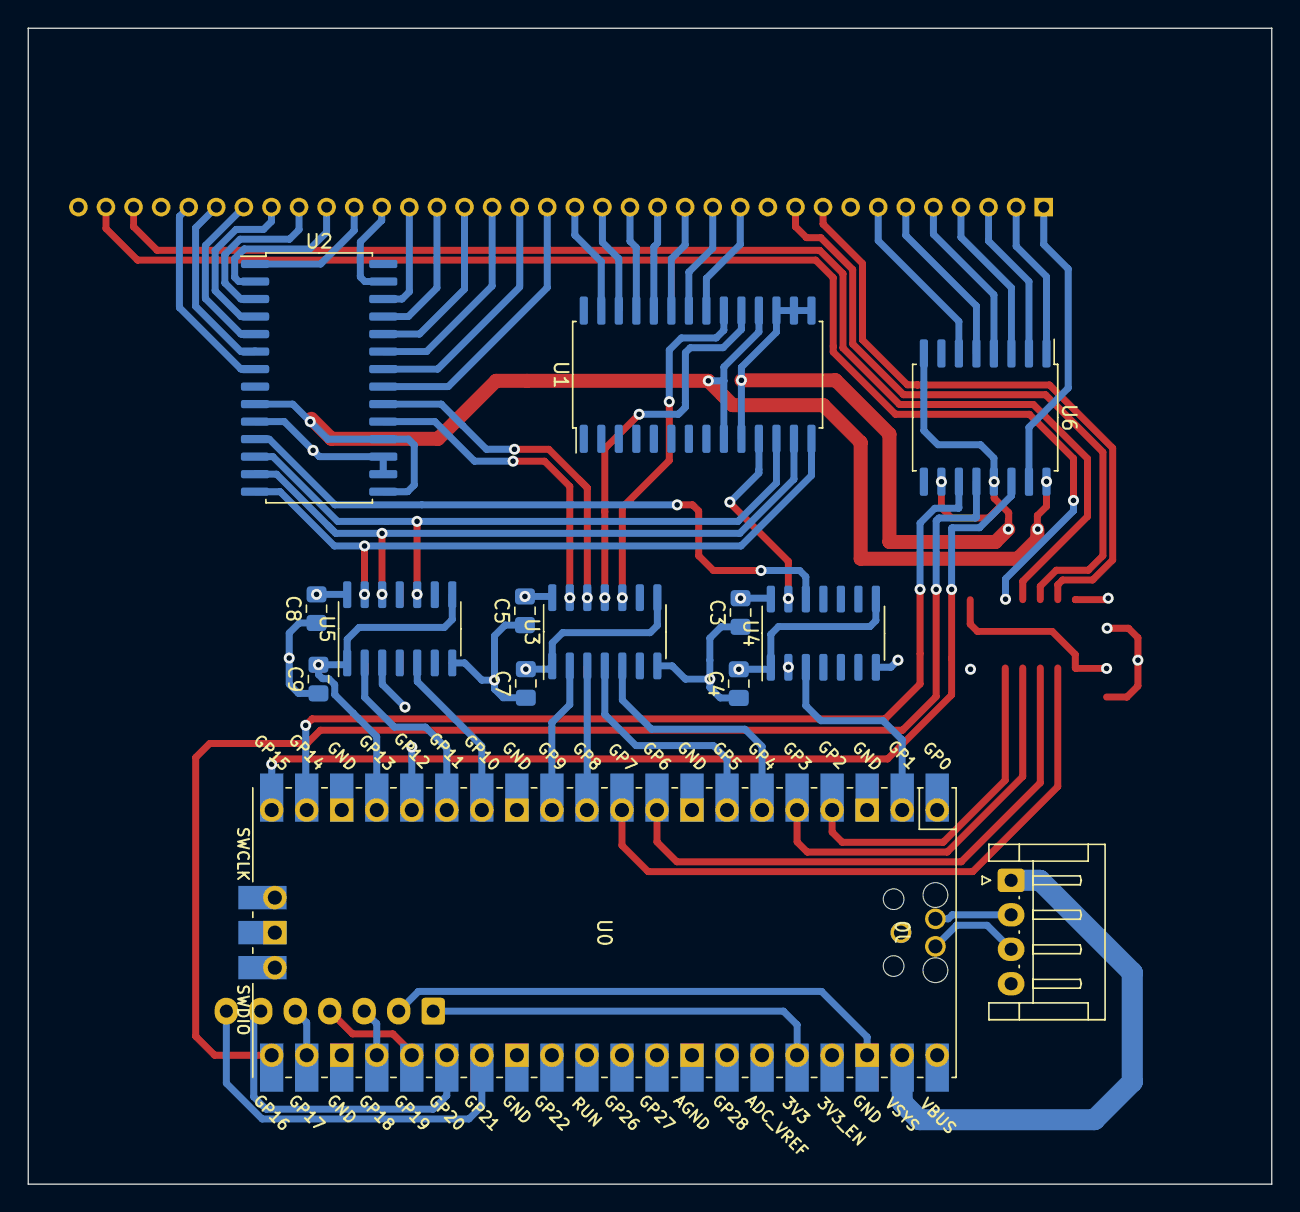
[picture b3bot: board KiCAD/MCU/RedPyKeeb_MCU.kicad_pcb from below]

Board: 4 copper layers, 90.2 x 83.8 mm, 22 parts (14 on the bottom side), 69 nets.

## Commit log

2021-03-07 Add initial files.
2021-03-07 Add some libraries for keyboard parts.
2021-03-07 Add license file. Add README.
2021-03-10 Update KiCAD files
2021-03-13 Update KiCAD files and README
2021-03-20 Update KiCAD files, hopefully a working board this time.
2021-03-21 Update KiCAD files to fix minor issues. Add initial release of firmware, not currently functioning.
2021-03-31 Update KiCAD files.
2021-04-06 Update firmware and KiCAD files.
2021-04-13 KiCAD and firmware updates, first working firmware and half way through a board rewire after the initial semi-working board. Firmware has no real LED control other than the power budget system and pi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
2021-04-14 Update KiCAD and firmware files. Firmware has had a little bit of work to make sending key data easier. PCB has been fully routed for the 4th time and should be good to test LEDs and a much more popu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
2021-04-16 Update KiCAD files for new BoM, new keyboard PCB and gerbers. Update Firmware to better support the keymap and for adding meta keys that drive the internal menu system to change values on the fly.
2021-04-17 Update Firmware to use more of the interrupt data to make finding which keys are pressed way faster. Add board preview file from KiCAD.
2021-04-17 Firmware update to add initial LED support for some form of animation.
2021-04-18 Fimware update, this is as fast as I can get the leds to animate and keys to not lag.
2021-04-30 Split the PCB into 2 PCBs to allow for replacement MCUs and MCU boards while being able to test on the same key matrix and LED PCB. Lots of changes for firmware, really this is just what I have made 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
2021-05-16 This is as-is before I test out a teensy MCU instead of the pico..
2021-05-16 Timings on the teensy are amazing, so this will be the MCU of choice. A little annoying as I loved the pico for the Pyco name, so I'll just have to come up with something else.
2021-06-16 Firmware is as-is for now, I've been testing PCB revisions and seeing what kind of latency I can poll the entire key matrix at KiCAD designs are looking really good now and I shoulld have parts in th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
2021-07-27 Latest KiCAD files and what ever I had for testing the old boards.
2021-09-01 NKRO is now supported and I've got what I believe to be working PCBs now
2021-09-25 Minimum viable product! I still need to work out a few things on the PCBs but its finally real!
2021-09-26 Add dip switch to allow for plug-in/boot time option selects. Add status light LEDs to be handled and actually reflect capslock and numlock status. Add tiny debounce which is enough on my prototype b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
2021-10-16 Fix issues found with MCU and mainboard PCBs. Adding whatever fiddling I had with firmware.
2021-10-17 Make more fixes and revisions to both PCBs, add in a pico for lighting and display functions and hook up an SPI bus with key event data.
2022-02-02 Allow for dual MCU for lighting/display and key management
2022-02-02 Update firmware deps
